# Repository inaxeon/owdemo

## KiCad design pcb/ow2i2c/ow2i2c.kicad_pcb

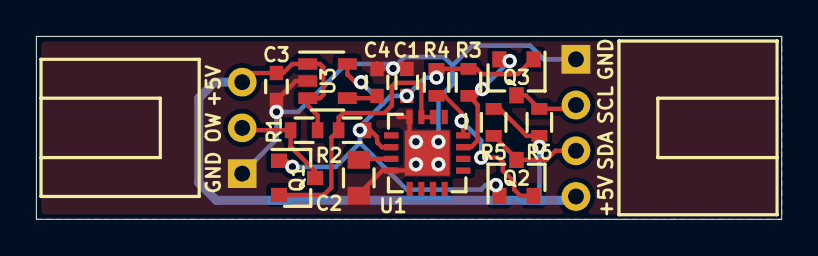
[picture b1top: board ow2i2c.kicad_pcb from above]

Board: 2 copper layers, 41.4 x 10.2 mm, 17 parts (0 on the bottom side), 11 nets.

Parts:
C1, C3: 0.1; C_0603
C2: 1uF; C_0805
C4: 0.01; C_0603
J1: BUS; 78208-103HLF
J2: I2C; 78208-104HLF
Q1, Q2, Q3: 2N7002; SOT-23
R1: NF; R_0603
R2, R3, R4: 4K7; R_0603
R5, R6: 2K2; R_0603
U1: DS28E17; QFN-16-1EP_4x4mm_Pitch0.65mm
U3: LP2985-3.3; SOT-23-5

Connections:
+3V3: C1.1, Q1.1, Q2.1, Q3.1, R2.1, R3.1, R4.1, U1.6, U3.5
/ONEWIRE: J1.2, Q1.3, R1.2
/SCL: J2.2, Q3.3, R6.2
/SCL3: Q3.2, R3.2, U1.15
/SDA: J2.3, Q2.3, R5.2
/SDA3: Q2.2, R4.2, U1.16
GND: C1.2, C2.2, C3.2, C4.2, J1.1, J2.1, U1.4, U1.8, U1.17, U3.2
unnamed: C2.1, U1.7
unnamed: C4.1, U3.4
unnamed: Q1.2, R2.2, U1.2, U1.3
VCC: C3.1, J1.3, J2.4, R1.1, R5.1, R6.1, U3.1, U3.3

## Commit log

2021-03-23 Fixed warning
2021-03-23 Clarified read lux function name, removed cruft, added message when read fails
2021-03-23 Simplify
2021-03-24 Fixed negative display
2021-03-24 Corrected file header comment
2021-04-16 Added MCP9808 via DS28E17
2021-04-16 Add gerbers for I2C adapter boards
